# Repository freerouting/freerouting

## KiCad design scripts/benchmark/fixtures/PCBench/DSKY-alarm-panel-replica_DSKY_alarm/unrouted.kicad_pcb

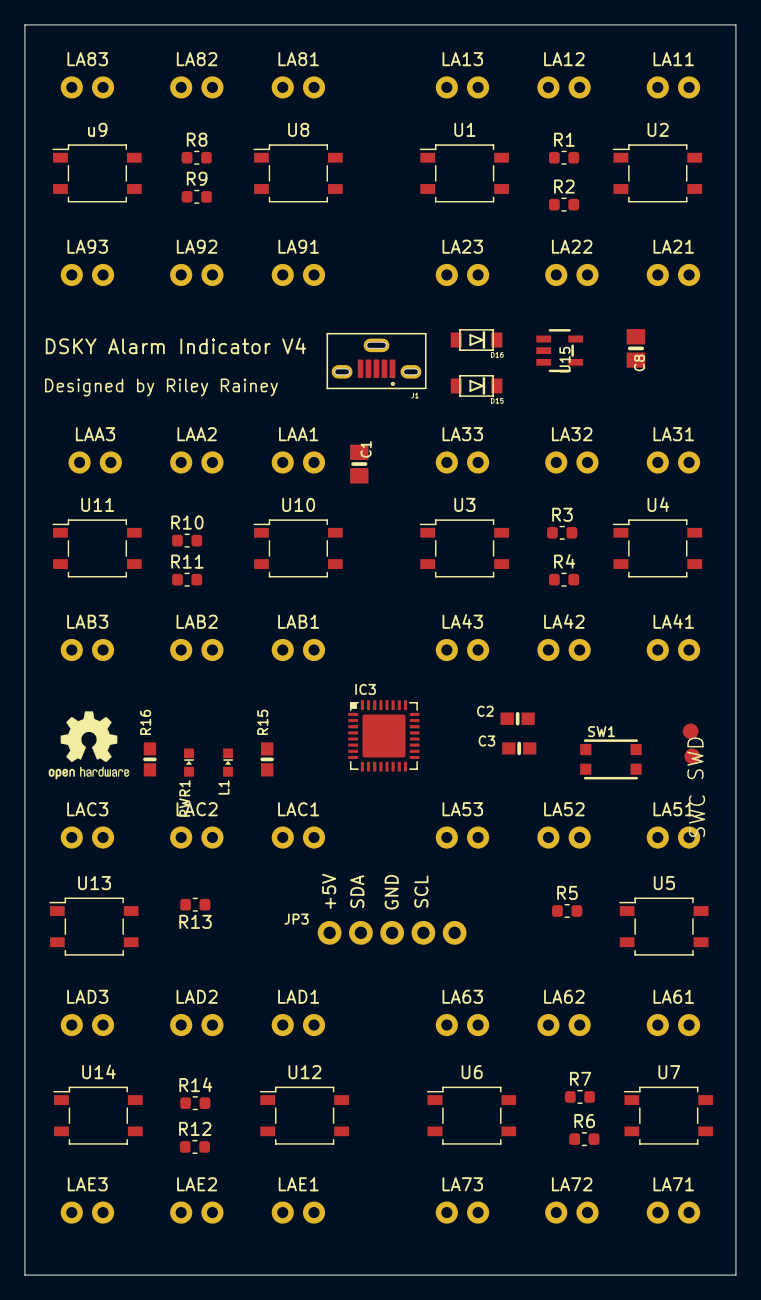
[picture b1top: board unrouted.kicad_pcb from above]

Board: 2 copper layers, 57.8 x 101.6 mm, 87 parts (0 on the bottom side), 58 nets, no tracks yet.

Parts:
C1, C8: 10uF; 0805-NO
C2, C3: 1uF; 0603-NO
D15, D16: SCHOTTKY; SOD-123FL
IC3: ATSAMD21E; QFN32_5MM
J1: 105133-0001-MOLEX-USB; MOLEX_105133-0001
JP3: HEADER-1X576MIL; 1X05_ROUND_76
L1: red; CHIPLED_0603_NOOUTLINE
LA11, LA12, LA13, LA21, LA22, LA23, LA31, LA32, LA33, LA41, LA42, LA43, LA51, LA52, LA53, LA61, LA62, LA63, LA71, LA72, LA73, LA81, LA82, LA83, LA91, LA92, LA93: Lamp; VCC7216-ND
LAA1, LAA2, LAA3: Lamp; VCC7216-ND
LAB1, LAB2, LAB3: Lamp; VCC7216-ND
LAC1, LAC2, LAC3: Lamp; VCC7216-ND
LAD1, LAD2, LAD3: Lamp; VCC7216-ND
LAE1, LAE2, LAE3: Lamp; VCC7216-ND
PWR1: green; CHIPLED_0603_NOOUTLINE
R1, R2, R3, R4, R5, R6, R7, R8, R9, R10, R11, R12, R13, R14: 1.1K; R_0603_1608Metric
R15: 1.5K; 0603-NO
R16: 10K; 0603-NO
SW1: reset; BTN_KMR2_4.6X2.8
SWC: TPB1,27; B1,27
SWD: TPB1,27; B1,27
U1, U2, U3, U4, U5, U6, U7, U8, U10, U11, U12, U13, U14: AQY232SZ; SO-4_4.4x4.3mm_P2.54mm
U15: AP2112K-3.3; SOT23-5
u9: AQY232SZ; SO-4_4.4x4.3mm_P2.54mm

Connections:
3.3V: C2.1, C8.1, IC3.9, IC3.30, R16.2, U15.5
+5V: D16.A, JP3.1, LA11.2, LA12.2, LA13.2, LA21.2, LA22.2, LA23.2, LA31.2, LA32.2, LA33.2, LA41.2, LA42.2, LA43.2, LA51.2, LA52.2, LA53.2, LA61.2, LA62.2, LA63.2, LA71.2, LA72.2, LA73.2, LA81.2, LA82.2, LA83.2, LA91.2, LA92.2, LA93.2, LAA1.2, LAA2.2, LAA3.2, LAB1.2, LAB2.2, LAB3.2, LAC1.2, LAC2.2, LAC3.2, LAD1.2, LAD2.2, LAD3.2, LAE1.2, LAE2.2, LAE3.2
/D0_A4_PA08_SDA: IC3.11, JP3.2
/D2_A1_PA09_SCL_MISO: IC3.12, JP3.4
/D+: IC3.24, J1.3
/D-: IC3.23, J1.2
/VOUT: C1.1, D15.C, D16.C, U15.1, U15.3
/~RESET: IC3.26, SW1.A, SW1.A'
GND: C1.2, C2.2, C3.2, C8.2, IC3.10, IC3.28, IC3.33, J1.5, J1.S3, JP3.3, L1.C, PWR1.C, SW1.B, SW1.B', U1.2, U1.3, U2.2, U2.3, U3.2, U3.3, U4.2, U4.3, U5.2, U5.3, U6.2, U6.3, U7.2, U7.3, U8.2, U8.3, U10.2, U10.3, U11.2, U11.3, U12.2, U12.3, U13.2, U13.3, U14.2, U14.3, U15.2, u9.2, u9.3
LA1_PA02: IC3.3, R1.1
LA2_PA03: IC3.4, R2.1
LA3_PA04: IC3.5, R3.1
LA4_P05: IC3.6, R4.1
LA5_PA19: IC3.20, R5.1
LA6_PA22: IC3.21, R6.1
LA7_PA23: IC3.22, R7.1
LA8_PA27: IC3.25, R8.1
LA9_PA11: IC3.14, R9.1
LA10_PA14: IC3.15, R10.1
LA11_PA15: IC3.16, R11.1
LA12_PA16: IC3.17, R12.1
LA13_PA17: IC3.18, R13.1
LA14_PA18: IC3.19, R14.1
unnamed: C3.1, IC3.29
unnamed: IC3.13, R15.2
unnamed: IC3.31, SWC.TP
unnamed: IC3.32, SWD.TP
unnamed: L1.A, R15.1
unnamed: LA11.1, LA12.1, LA13.1, U1.4
unnamed: LA21.1, LA22.1, LA23.1, U2.4
unnamed: LA31.1, LA32.1, LA33.1, U3.4
unnamed: LA41.1, LA42.1, LA43.1, U4.4
unnamed: LA51.1, LA52.1, LA53.1, U5.4
unnamed: LA61.1, LA62.1, LA63.1, U6.4
unnamed: LA71.1, LA72.1, LA73.1, U7.4
unnamed: LA81.1, LA82.1, LA83.1, U8.4
unnamed: LA91.1, LA92.1, LA93.1, u9.4
unnamed: LAA1.1, LAA2.1, LAA3.1, U10.4
unnamed: LAB1.1, LAB2.1, LAB3.1, U11.4
unnamed: LAC1.1, LAC2.1, LAC3.1, U12.4
unnamed: LAD1.1, LAD2.1, LAD3.1, U13.4
unnamed: LAE1.1, LAE2.1, LAE3.1, U14.4
unnamed: PWR1.A, R16.1
unnamed: R1.2, U1.1
unnamed: R2.2, U2.1
unnamed: R3.2, U3.1
unnamed: R4.2, U4.1
unnamed: R5.2, U5.1
unnamed: R6.2, U6.1
unnamed: R7.2, U7.1
unnamed: R8.2, U8.1
unnamed: R9.2, u9.1
unnamed: R10.2, U10.1
unnamed: R11.2, U11.1
unnamed: R12.2, U12.1
unnamed: R13.2, U13.1
unnamed: R14.2, U14.1
VBUS: D15.A, J1.1

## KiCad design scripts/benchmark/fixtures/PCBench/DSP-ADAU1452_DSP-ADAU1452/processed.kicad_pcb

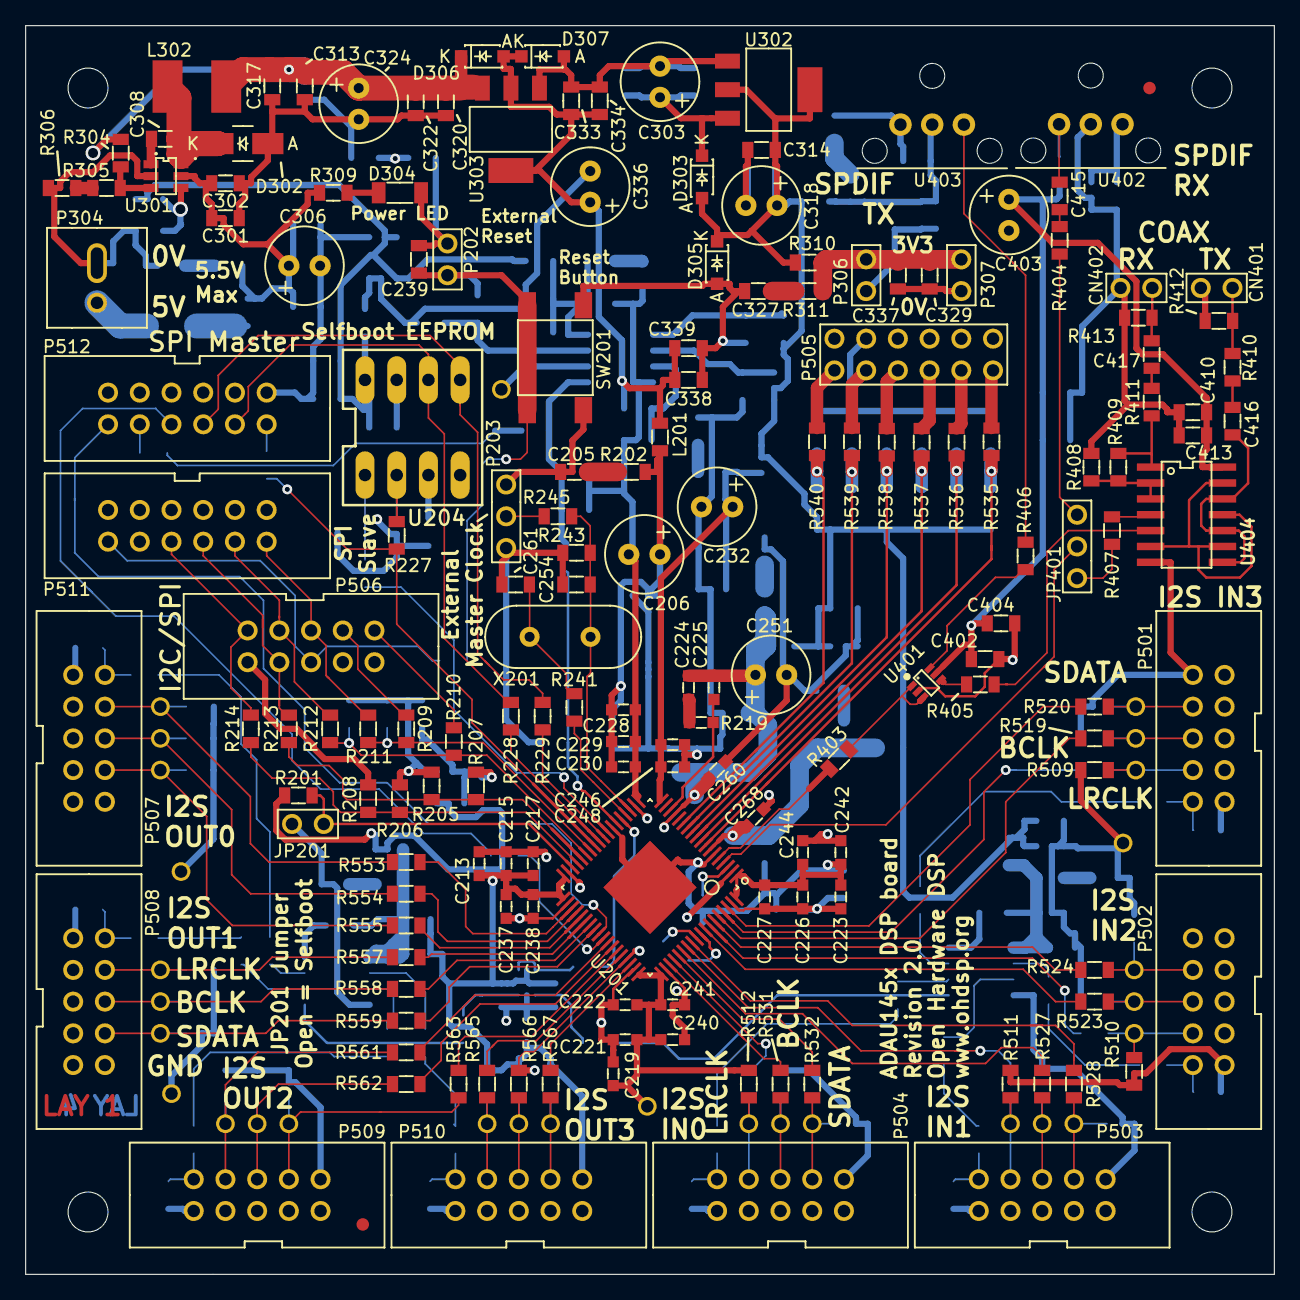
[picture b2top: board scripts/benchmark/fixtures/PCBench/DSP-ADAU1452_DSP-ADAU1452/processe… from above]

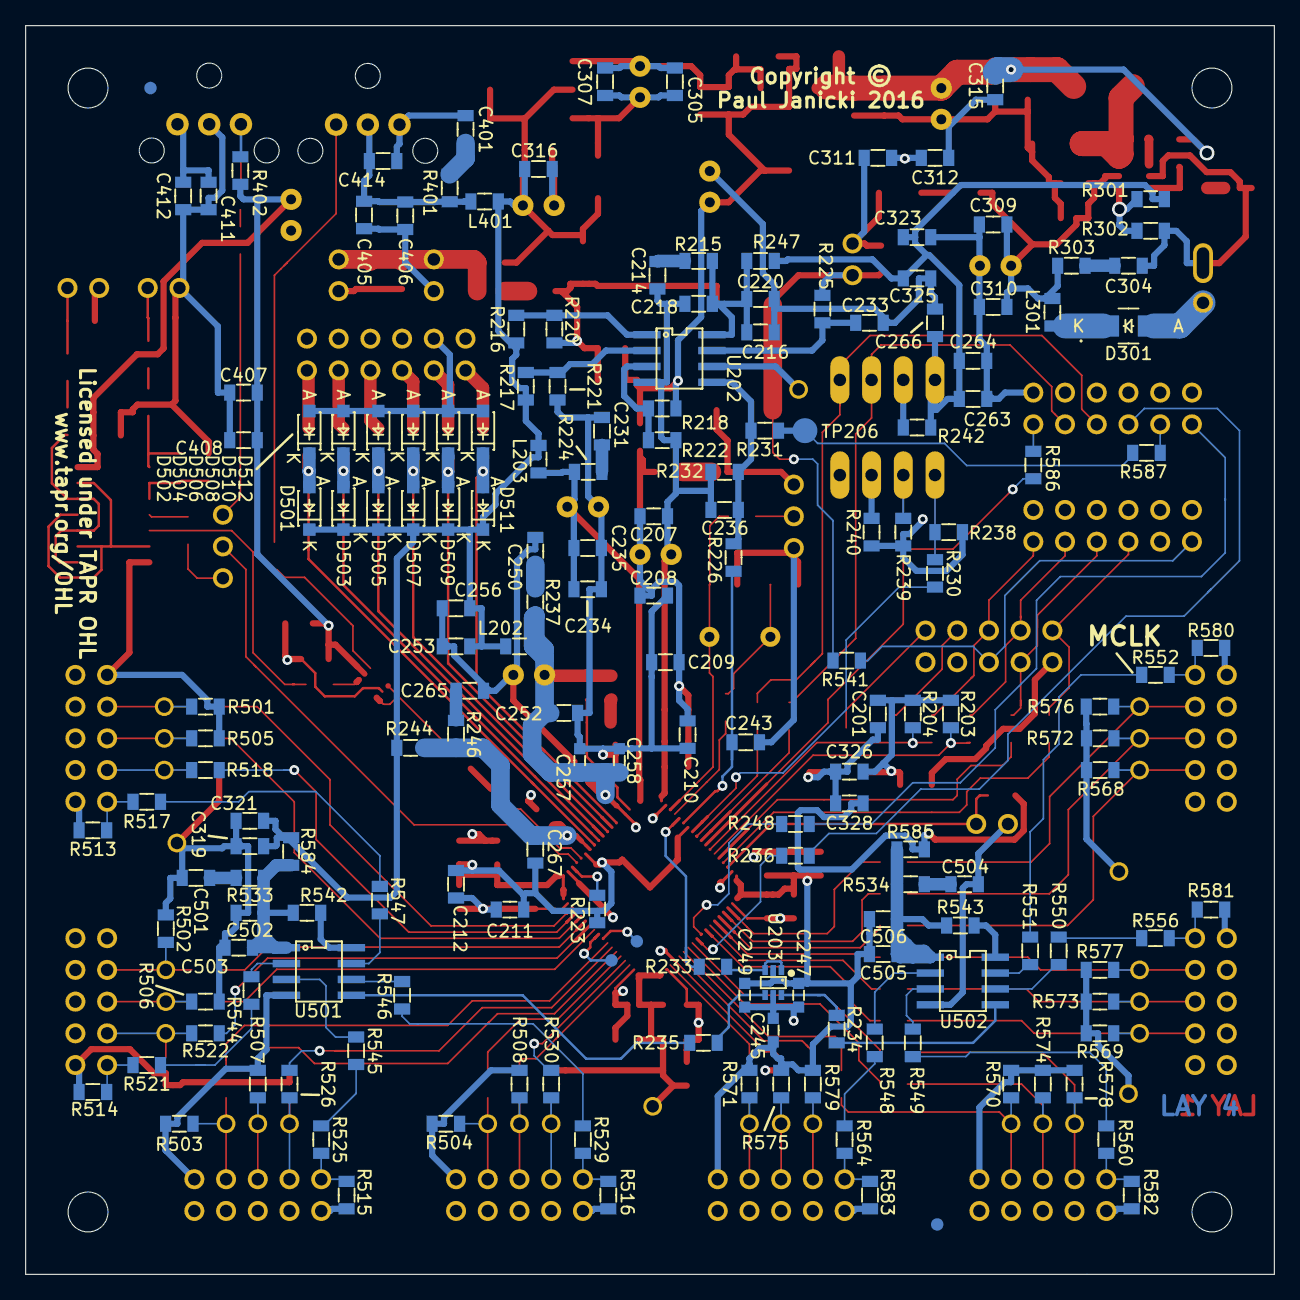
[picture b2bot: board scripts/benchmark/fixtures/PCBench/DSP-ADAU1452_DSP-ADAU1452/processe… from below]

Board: 4 copper layers, 100.0 x 100.0 mm, 377 parts (177 on the bottom side), 190 nets.

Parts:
C201, C208, C210, C212, C218, C233, C235, C236, C239, C243, C253, C264, C302, C307, C310, C314, C317, C319, C320, C323, C326, C329, C333, C338, C402, C406, C412, C413, C414, C416, C417, C503, C506: 100n; SMD-0805
C205, C214, C231, C250, C265, C304, C327, C401, C501, C504: 100p; SMD-0805
C206, C232, C251, C303, C306, C318, C324, C336, C403: 220u; CAP-TH-D6.3mmP2.5mm
C207, C234, C252, C267, C301, C305, C309, C313, C315, C316, C322, C334, C405, C502, C505: 22u; SMD-0805
C209, C211, C216, C256, C266, C321, C325, C328, C337, C339, C404, C410, C411: 10u; SMD-0805
C213, C219, C223, C228, C237, C240, C242, C245, C246, C257: 1u; SMD-0603
C215, C221, C226, C229, C238, C241, C244, C247, C248, C258, C268: 100n; SMD-0603
C217, C222, C227, C230, C249, C260: 10n; SMD-0603
C220, C263, C308, C415: 10n; SMD-0805
C224: 5n6; SMD-0603
C225: 150p; SMD-0603
C254, C261: 33p; SMD-0805
C311, C312, C407, C408: N/F; SMD-0805
CN401, CN402: COAX; CONN_SIL_2_1MM
D301, D302: B240A; DIODE-SMA
D303, D305, D306, D307, D501, D502, D503, D504, D505, D506, D507, D508, D509, D510, D511, D512: SS14L; DIODE-SOD-123
D304: Green LED 1206; SMD-1206
FID1, FID2, FID3, FID4: MNT_HOLE; FID-1MM-3MM
JP201: CONN_2x1; CONN_SIL_2_1MM
JP401: CONN_3x1; CONN_SIL_3_1MM
L201, L202, L203, L301, L401: 600R@100MHz; SMD-0805
L302: TYS50404R7N-10; IND-TYS5040-HS
MNT301, MNT302, MNT303, MNT304: MNT_HOLE; MNT_HOLE_3.2mm
P202, P306, P307: CONN_2x1; CONN_SIL_2_1MM
P203: CONN_3x1; CONN_SIL_3_1MM
P304: CONN_2x1; CONN-2WAY-2.54mm-3.81mm-SPACING
P501, P502, P503, P504, P506, P507, P508, P509, P510: CONN_02X05; CONN_DIL_2X5_BOX_1MM
P505: CONN_02X06; CONN_DIL_2X6_1MM
P511, P512: CONN_02X06; CONN_DIL_2X6_BOX_1MM
R201, R225, R542, R543: 1k; SMD-0805
R202, R215, R224, R237, R246, R303, R311, R401, R533, R534: 47; SMD-0805
R203, R204, R205, R206, R207, R208, R209, R210, R220, R239, R243, R245, R501, R502, R503, R504, R505, R506, R507, R508, R509, R510, R511, R512, R513, R514, R515, R516, R568, R569, R570, R571, R572, R573, R574, R575, R576, R577, R578, R579, R580, R581, R582, R583: N/F; SMD-0805
R211, R227, R228, R229, R230, R233, R234, R235, R236, R248, R403, R404, R405, R406, R407, R413, R544, R545, R546, R547, R548, R549, R550, R551, R553, R554, R555, R557, R558, R559, R561, R562, R563, R565, R566, R567: 75; SMD-0805
R212, R213, R214, R216, R223, R306, R517, R518, R519, R520, R521, R522, R523, R524, R525, R526, R527, R528, R529, R530, R531, R532, R541, R552, R556, R560, R564, R586, R587: 0; SMD-0805
R217: 12k; SMD-0805
R218: 3k3; SMD-0805
R219: 4k3; SMD-0603
R221: 3k; SMD-0805
R222: 3k6; SMD-0805
R226, R231, R241, R411: 100; SMD-0805
R232: 100k; SMD-0805
R238, R240, R242, R302, R402, R408, R409: 10k; SMD-0805
R244, R247, R310, R584, R585: 1; SMD-0805
R301: 16k; SMD-0805
R304: 24k; SMD-0805
R305: 15k; SMD-0805
R309: 470; SMD-0805
R410: 360; SMD-0805
R412: 91; SMD-0805
R535, R536, R537, R538, R539, R540: 4k7; SMD-0805
SW201: SWITCH; SW_TACT_SMD
TP201, TP501, TP502, TP503, TP504, TP505, TP506, TP507, TP508, TP509, TP510, TP511, TP512, TP513, TP514, TP515, TP516, TP517, TP518, TP519, TP520, TP521, TP522, TP523, TP524, TP525, TP526, TP527, TP528: PIN; TP-TH-1mm
TP204, TP205: PIN; TP-1mm
TP206: PIN; TP-2mm
U201: ADAU1452WBCPZ; IC-LFCSP72-HANDFIT
U202: ADM13307-5ARZ; IC_SOIC_8
U203: NC7WZ17P6X; IC-SC70-6
U204: 25AA1024; IC_DIP_8
U301: ADP2301AUJZ; IC-SOT23-6
U302: TLV1117LV33DCY; IC-SOT-223
U303: TLV1117LV12DCY; IC-SOT-223
U401: NC7WZ16P6X; IC-SC70-6
U402: IC-SPDIF-RX-OPTO; IC_SPDIF_OPTO
U403: IC-SPDIF-TX-OPTO; IC_SPDIF_OPTO
U404: 74HC04; IC_SOIC_14
U501, U502: NB3L553; IC_SOIC_8
X201: 24M576; XTAL_HC49_TH

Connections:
/ADAU1452/ADAU_SPDIF_RX: JP401.2, U201.4
/ADAU1452/ADAU_SPDIF_TX: R403.2, U201.5
/ADAU1452/ADCIN_BCLK0: R531.2, U201.57
/ADAU1452/ADCIN_BCLK1: R527.2, U201.60
/ADAU1452/ADCIN_BCLK2: R523.2, U201.65
/ADAU1452/ADCIN_BCLK3: R519.2, U201.68
/ADAU1452/ADCIN_LRCLK0: R530.2, U201.58
/ADAU1452/ADCIN_LRCLK1: R526.2, U201.61
/ADAU1452/ADCIN_LRCLK2: R522.2, U201.66
/ADAU1452/ADCIN_LRCLK3: R518.2, U201.69
/ADAU1452/ADCIN_SDATA0: R532.2, U201.59
/ADAU1452/ADCIN_SDATA1: R528.2, U201.62
/ADAU1452/ADCIN_SDATA2: R524.2, U201.67
/ADAU1452/ADCIN_SDATA3: R520.2, U201.70
/ADAU1452/AVDD: C267.1, C268.1, R244.1, R246.1, U201.7
/ADAU1452/DACOUT_BCLK0: R554.1, U201.40
/ADAU1452/DACOUT_BCLK1: R558.1, U201.43
/ADAU1452/DACOUT_BCLK2: R562.1, U201.48
/ADAU1452/DACOUT_BCLK3: R566.1, U201.51
/ADAU1452/DACOUT_LRCLK0: R553.1, U201.39
/ADAU1452/DACOUT_LRCLK1: R557.1, U201.42
/ADAU1452/DACOUT_LRCLK2: R561.1, U201.47
/ADAU1452/DACOUT_LRCLK3: R565.1, U201.50
/ADAU1452/DACOUT_SDATA0: R555.1, U201.41
/ADAU1452/DACOUT_SDATA1: R559.1, U201.44
/ADAU1452/DACOUT_SDATA2: R563.1, U201.49
/ADAU1452/DACOUT_SDATA3: R567.1, U201.52
/ADAU1452/DSP_RESET: C243.1, R226.1, U201.24
/ADAU1452/DVDD: C206.1, C207.1, C208.1, C209.1, C210.1, C211.1, C212.1, C213.1, C215.1, C217.1, C219.1, C221.1, C222.1, C223.1, C226.1, C227.1, C228.1, C229.1, C230.1, L201.2, R202.1, U201.20, U201.35, U201.53, U201.71
/ADAU1452/GLB_RESET: R231.1, R587.2, TP206.1
/ADAU1452/I2C_SCL: P506.1, R210.1
/ADAU1452/I2C_SDA: P506.3, R209.1
/ADAU1452/IOVDD: C232.1, C234.1, C235.1, C237.1, C238.1, C240.1, C241.1, C242.1, C244.1, C245.1, C246.1, C247.1, C248.1, C249.1, L203.2, R224.1, U201.2, U201.18, U201.38, U201.56, U203.5
/ADAU1452/MAN_RST_IN: C239.1, P202.1, R225.2, R541.2, SW201.1
/ADAU1452/MCLK: R235.1, U501.5
/ADAU1452/MCLK2: R234.1, U502.5
/ADAU1452/MCLK_ADAU: R233.2, U201.23
/ADAU1452/MISO/SDA: R204.2, R209.2, R211.2, U201.30
/ADAU1452/MOSI/ADDR1: R205.2, R207.2, R213.2, U201.32
/ADAU1452/M_SS: R230.2, R238.2, U204.1
/ADAU1452/PVDD: C224.1, C225.1, C251.1, C252.1, C257.1, C258.1, C260.1, L202.2, R237.1, U201.15
/ADAU1452/SCLK/SCL: R203.2, R210.2, R212.2, U201.31
/ADAU1452/SELFBOOT: JP201.1, R201.2, U201.34
/ADAU1452/SPI_MISO: P506.5, P511.2, R211.1
/ADAU1452/SPI_MOSI: P506.8, P511.6, R213.1
/ADAU1452/SPI_SCLK: P506.7, P511.4, R212.1
/ADAU1452/SPI_SS: P506.9, P511.8, R214.1
/ADAU1452/SS/ADDR0: R206.2, R208.2, R214.2, U201.33
/ADAU1452/XTALIN: C254.1, R243.1, R245.1, U201.21, X201.1
/ADAU1452/XTALOUT: R241.1, U201.22
/Connectors/AUXADCIN_1: D501.1, D502.2, R535.2, U201.8
/Connectors/AUXADCIN_2: D503.1, D504.2, R536.2, U201.9
/Connectors/AUXADCIN_3: D505.1, D506.2, R537.2, U201.10
/Connectors/AUXADCIN_4: D507.1, D508.2, R538.2, U201.11
/Connectors/AUXADCIN_5: D509.1, D510.2, R539.2, U201.12
/Connectors/AUXADCIN_6: D511.1, D512.2, R540.2, U201.13
/Connectors/I2C_RST: P506.6, P511.12, R541.1
/Connectors/MCLKA1: R529.2, R546.1
/Connectors/MCLKA2: R525.2, R545.1
/Connectors/MCLKA3: R521.2, R544.1
/Connectors/MCLKA4: R517.2, R547.1
/Connectors/MCLKB1: R551.1, R552.1
/Connectors/MCLKB2: R550.1, R556.1
/Connectors/MCLKB3: R549.1, R560.1
/Connectors/MCLKB4: R548.1, R564.1
/Connectors/M_MUTE: P512.12, R248.2
/Connectors/M_SPI_MISO: R227.1, R586.2, U201.29
/Connectors/M_SPI_MOSI: P512.6, R229.2, U204.5
/Connectors/M_SPI_SCLK: P512.4, R228.2, U204.6
/Connectors/M_SPI_SS: P512.8, R236.2
/Power Supply/2V1: C313.1, C315.1, C317.1, C320.1, C322.1, C324.1, D306.2, L302.2, R304.2, U303.3
GNDD: C201.2, C205.2, C206.2, C207.2, C208.2, C209.2, C210.2, C211.2, C212.2, C213.2, C214.2, C215.2, C216.2, C217.2, C218.2, C219.2, C220.2, C221.2, C222.2, C223.2, C226.2, C227.2, C228.2, C229.2, C230.2, C231.2, C232.2, C233.2, C234.2, C235.2, C236.2, C237.2, C238.2, C239.2, C240.2, C241.2, C242.2, C243.2, C244.2, C245.2, C246.2, C247.2, C248.2, C249.2, C250.2, C251.2, C252.2, C253.2, C254.2, C256.2, C257.2, C258.2, C260.2, C261.2, C263.2, C264.2, C265.2, C266.2, C267.2, C268.2, C301.1, C302.1, C303.2, C304.2, C305.2, C306.2, C307.2, C309.1, C310.1, C311.1, C312.1, C313.2, C314.2, C315.2, C316.2, C317.2, C318.2, C319.2, C320.2, C321.2, C322.2, C323.2, C324.2, C325.2, C326.2, C327.2, C328.2, C329.2, C333.2, C334.2, C336.2, C337.2, C338.2, C339.2, C401.2, C402.2, C403.2, C404.2, C405.2, C406.2, C407.2, C408.2, C410.2, C411.2, C412.2, C413.2, C414.2, C501.2, C502.2, C503.2, C504.2, C505.2, C506.2, CN401.2, CN402.2, D302.1, D304.2, D305.1, D307.1, D502.1, D504.1, D506.1, D508.1, D510.1, D512.1, JP201.2, P202.2, P203.1, P203.3, P304.2, P306.2, P307.2, P501.1, P501.3, P501.5, P501.7, P501.9, P501.10, P502.1, P502.3, P502.5, P502.7, P502.9, P502.10, P503.1, P503.3, P503.5, P503.7, P503.9, P503.10, P504.1, P504.3, P504.5, P504.7, P504.9, P504.10, P505.1, P505.3, P505.5, P505.7, P505.9, P505.11, P506.10, P507.1, P507.3, P507.5, P507.7, P507.9, P507.10, P508.1, P508.3, P508.5, P508.7, P508.9, P508.10, P509.1, P509.3, P509.5, P509.7, P509.9, P509.10, P510.1, P510.3, P510.5, P510.7, P510.9, P510.10, P511.1, P511.3, P511.5, P511.7, P511.9, P511.11, P512.1, P512.3, P512.5, P512.7, P512.9, P512.11, R207.1, R208.1, R220.1, R221.1, R222.1, R223.1, R232.1, R243.2, R302.1, R306.1, R408.1, R412.1, R413.1, R501.1, R502.1, R503.1, R504.1, R505.1, R506.1, R507.1, R508.1, R509.1, R510.1, R511.1, R512.1, R513.1, R514.1, R515.1, R516.1, R568.1, R569.1, R570.1, R571.1, R572.1, R573.1, R574.1, R575.1, R576.1, R577.1, R578.1, R579.1, R580.1, R581.1, R582.1, R583.1, SW201.2, TP513.1, TP514.1, TP515.1, TP516.1, U201.1, U201.6, U201.19, U201.25, U201.36, U201.37, U201.54, U201.55, U201.72, U201.EP1, U202.4, U203.2, U204.4, U301.2, U302.1, U303.1, U401.2, U402.2, U403.3, U404.7, U501.4, U502.4
unnamed: C205.1, R202.2
unnamed: C214.1, R215.2
unnamed: C216.1, C218.1, C220.1, R215.1, R247.1, U202.8
unnamed: C224.2, R219.1
unnamed: C225.2, R219.2, U201.16
unnamed: C231.1, R224.2
unnamed: C233.1, R225.1, U202.7
unnamed: C236.1, R226.2, R231.2, R232.2, U202.5
unnamed: C250.1, R237.2
unnamed: C261.1, R241.2, X201.2
unnamed: C265.1, R246.2
unnamed: C304.1, R303.2
unnamed: C308.1, U301.1
unnamed: C308.2, D302.2, L302.1, U301.6
unnamed: C327.1, R311.2
unnamed: C329.1, C337.1, P306.1, P307.1, R310.1, R311.1
unnamed: C401.1, R401.2
unnamed: C402.1, C403.1, C404.1, C405.1, C406.1, C407.1, C408.1, C410.1, C411.1, C412.1, C413.1, C414.1, L401.2, R401.1, R402.1, U401.5, U402.1, U403.2, U404.14
unnamed: C415.1, R404.2
unnamed: C415.2, R402.2, U402.3
unnamed: C416.1, R410.2
unnamed: C416.2, U404.8, U404.10, U404.12
unnamed: C417.1, R411.2
unnamed: C417.2, CN402.1, R413.2
unnamed: C501.1, R533.2
unnamed: C502.1, C503.1, R533.1, R542.2, R584.2, U501.1
unnamed: C504.1, R534.2
unnamed: C505.1, C506.1, R534.1, R543.2, R585.2, U502.1
unnamed: CN401.1, R410.1, R412.2
unnamed: D301.1, P304.1
unnamed: D301.2, L301.1
unnamed: D304.1, R309.2
unnamed: JP401.1, R404.1
unnamed: JP401.3, R407.2
unnamed: P203.2, R245.2
unnamed: P501.2, R513.2, R517.1
unnamed: P501.4, R509.2, R518.1, TP501.1
unnamed: P501.6, R505.2, R519.1, TP505.1
unnamed: P501.8, R501.2, R520.1, TP506.1
unnamed: P502.2, R514.2, R521.1
unnamed: P502.4, R510.2, R522.1, TP502.1
unnamed: P502.6, R506.2, R523.1, TP507.1
unnamed: P502.8, R502.2, R524.1, TP508.1
unnamed: P503.2, R515.2, R525.1
unnamed: P503.4, R511.2, R526.1, TP503.1
unnamed: P503.6, R507.2, R527.1, TP509.1
unnamed: P503.8, R503.2, R528.1, TP510.1
unnamed: P504.2, R516.2, R529.1
unnamed: P504.4, R512.2, R530.1, TP504.1
unnamed: P504.6, R508.2, R531.1, TP511.1
unnamed: P504.8, R504.2, R532.1, TP512.1
unnamed: P505.2, R535.1
unnamed: P505.4, R536.1
unnamed: P505.6, R537.1
unnamed: P505.8, R538.1
unnamed: P505.10, R539.1
unnamed: P505.12, R540.1
unnamed: P507.2, R552.2, R580.2
unnamed: P507.4, R553.2, R576.2, TP517.1
unnamed: P507.6, R554.2, R572.2, TP521.1
unnamed: P507.8, R555.2, R568.2, TP522.1
unnamed: P508.2, R556.2, R581.2
unnamed: P508.4, R557.2, R577.2, TP518.1
unnamed: P508.6, R558.2, R573.2, TP523.1
unnamed: P508.8, R559.2, R569.2, TP524.1
unnamed: P509.2, R560.2, R582.2
unnamed: P509.4, R561.2, R578.2, TP519.1
unnamed: P509.6, R562.2, R574.2, TP525.1
unnamed: P509.8, R563.2, R570.2, TP526.1
unnamed: P510.2, R564.2, R583.2
unnamed: P510.4, R565.2, R579.2, TP520.1
unnamed: P510.6, R566.2, R575.2, TP527.1
unnamed: P510.8, R567.2, R571.2, TP528.1
unnamed: P512.2, R586.1
unnamed: P512.10, R587.1
unnamed: R216.2, R220.2, U202.1
unnamed: R217.2, R221.2, U202.2
unnamed: R218.2, R222.2, U202.3
unnamed: R223.2, U201.3
unnamed: R227.2, R239.2, U204.2
unnamed: R228.1, U201.28
unnamed: R229.1, U201.27
unnamed: R230.1, U201.26
unnamed: R233.1, U203.1, U203.3
unnamed: R234.2, U203.6
unnamed: R235.2, U203.4
unnamed: R236.1, U201.46
unnamed: R240.2, U204.3
unnamed: R242.2, U204.7
unnamed: R248.1, U201.45
unnamed: R301.1, R302.2, U301.4
unnamed: R304.1, R305.2, U301.3
unnamed: R305.1, R306.2
unnamed: R403.1, U401.1, U401.3
unnamed: R405.1, U404.5
unnamed: R405.2, U401.4
unnamed: R406.1, U401.6
unnamed: R406.2, U403.1
unnamed: R407.1, U404.4
unnamed: R408.2, R409.1, U404.2, U404.3
unnamed: R409.2, R411.1, U404.1
unnamed: R542.1, U501.8
unnamed: R543.1, U502.8
unnamed: R544.2, U501.2
unnamed: R545.2, U501.3
unnamed: R546.2, U501.6
unnamed: R547.2, U501.7
unnamed: R548.2, U502.2
unnamed: R549.2, U502.3
unnamed: R550.2, U502.6
unnamed: R551.2, U502.7
unnamed: TP201.1, U202.6
unnamed: TP204.1, U201.64
unnamed: TP205.1, U201.63
unnamed: U404.6, U404.9, U404.11, U404.13
VAA: C201.1, C253.1, C256.1, C263.1, C264.1, C266.1, C314.1, C316.1, C318.1, C319.1, C321.1, C323.1, C325.1, C326.1, C328.1, D303.1, D305.2, D501.2, D503.2, D505.2, D507.2, D509.2, D511.2, L202.1, L203.1, L401.1, R201.1, R203.1, R204.1, R205.1, R206.1, R216.1, R217.1, R238.1, R239.1, R240.1, R242.1, R244.2, R247.2, R301.2, R310.2, R584.1, R585.1, U204.8, U302.2
VCC: C301.2, C302.2, C303.1, C305.1, C306.1, C307.1, C309.2, C310.2, C311.2, C312.2, D303.2, L301.2, R303.1, R309.1, U301.5, U302.3
VDD: C333.1, C334.1, C336.1, C338.1, C339.1, D306.1, D307.2, L201.1, R218.1, U303.2

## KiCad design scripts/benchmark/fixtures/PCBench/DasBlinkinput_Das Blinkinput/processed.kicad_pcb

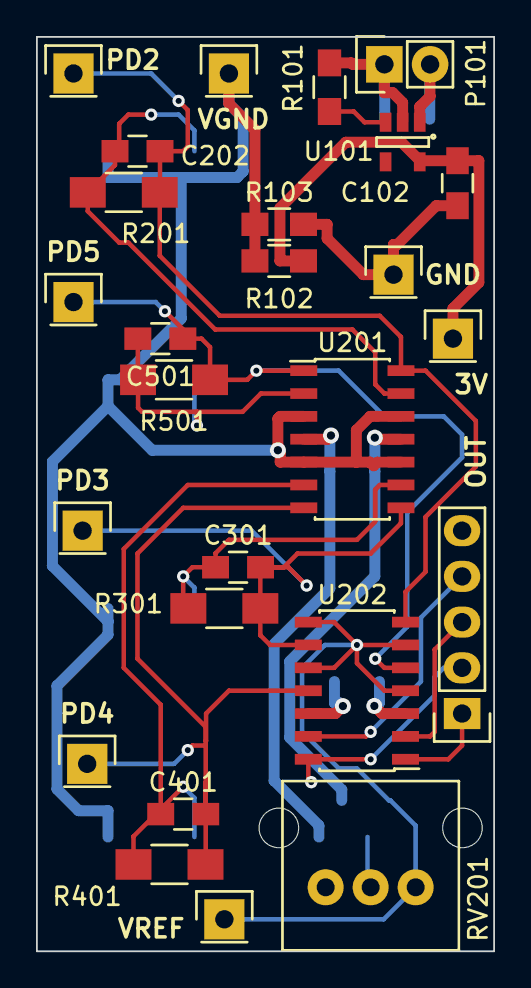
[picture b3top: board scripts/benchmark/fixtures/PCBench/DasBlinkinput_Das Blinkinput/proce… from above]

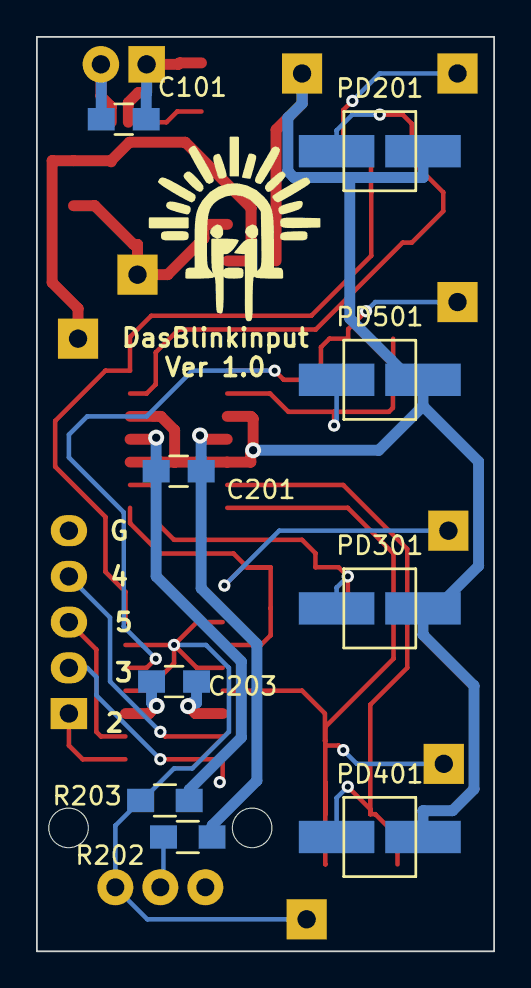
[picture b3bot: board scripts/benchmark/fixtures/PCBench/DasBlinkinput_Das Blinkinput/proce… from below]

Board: 4 copper layers, 25.4 x 50.8 mm, 35 parts (9 on the bottom side), 19 nets.

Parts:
C101, C102: 1U; C_0805_HandSoldering
C201, C203: .1U; C_0805_HandSoldering
C202, C301, C401, C501: 100p; C_0805_HandSoldering
P101: CONN_01X02; Pin_Header_Straight_1x02
P102, P103, P104, P106, P201, P301, P401, P501: CONN_01X01; Pin_Header_Straight_1x01
P105: CONN_01X05; Pin_Header_Straight_1x05
PD201, PD301, PD401, PD501: VBPW34SR; VPW34SR*
R101: 0; R_0805_HandSoldering
R102, R103, R202, R203: 10K; R_0805_HandSoldering
R201, R301, R401, R501: 1MEG; R_1206_HandSoldering
RV201: POT; P090L-02F25BR10K
U101: LP2980IM5-3.0/NOPB; SOT-23-5
U201: MCP6404; SOIC-14_3.9x8.7mm_Pitch1.27mm
U202: LM339; SOIC-14_3.9x8.7mm_Pitch1.27mm

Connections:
3V: C102.1, C201.2, C203.2, P103.1, R102.1, R203.2, U101.5, U201.4, U202.3
/Channel1Photodetect/PD2: P105.1, U202.1
/Channel2Photodetect/PD3: P105.2, U202.14
/Channel2Photodetect/REF_IN: P106.1, R202.2, RV201.3, U202.4, U202.6, U202.8, U202.10
/Channel3Photodetect/PD5: P105.3, U202.2
/Channel4Photodetect/PD4: P105.4, U202.13
GND: C101.2, C102.2, C201.1, C203.1, P101.1, P104.1, P105.5, R101.2, R103.2, R202.1, U101.2, U201.11, U202.12
unnamed: C101.1, P101.2, U101.1
unnamed: C202.1, P201.1, R201.1, U201.14, U202.7
unnamed: C202.2, PD201.2, R201.2, U201.13
unnamed: C301.1, P301.1, R301.1, U201.8, U202.9
unnamed: C301.2, PD301.2, R301.2, U201.9
unnamed: C401.1, P401.1, R401.1, U201.7, U202.11
unnamed: C401.2, PD401.2, R401.2, U201.6
unnamed: C501.1, P501.1, R501.1, U201.1, U202.5
unnamed: C501.2, PD501.2, R501.2, U201.2
unnamed: R101.1, U101.3
unnamed: R203.1, RV201.2
VGND: P102.1, PD201.1, PD301.1, PD401.1, PD501.1, R102.2, R103.1, U201.3, U201.5, U201.10, U201.12

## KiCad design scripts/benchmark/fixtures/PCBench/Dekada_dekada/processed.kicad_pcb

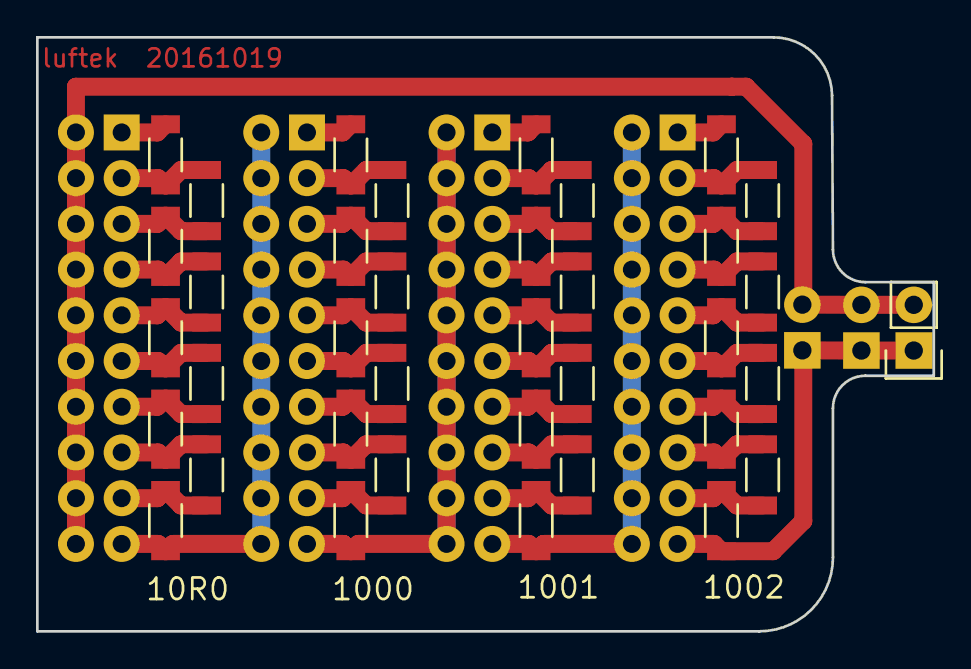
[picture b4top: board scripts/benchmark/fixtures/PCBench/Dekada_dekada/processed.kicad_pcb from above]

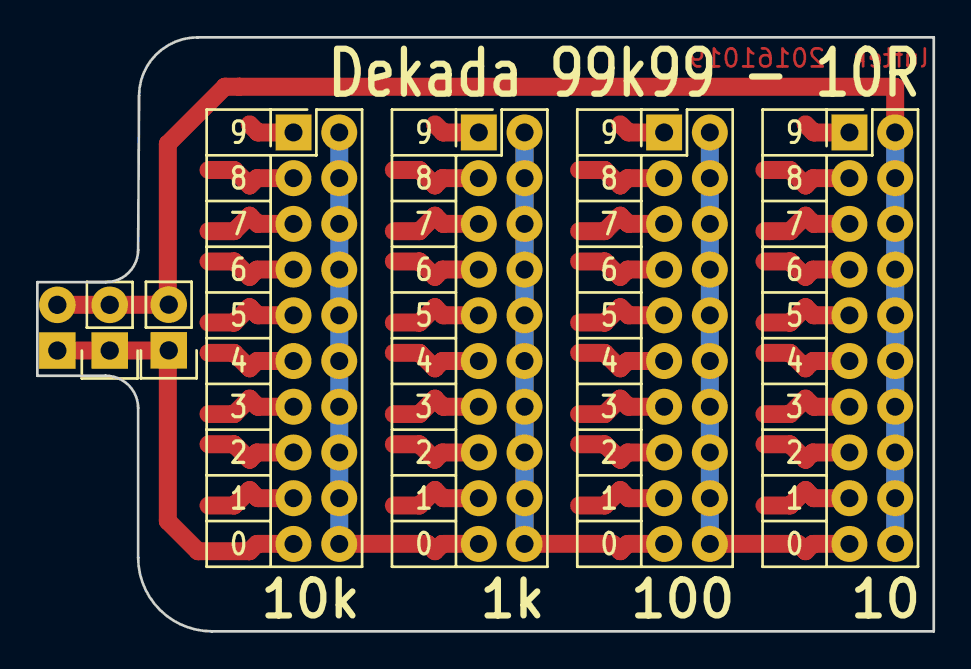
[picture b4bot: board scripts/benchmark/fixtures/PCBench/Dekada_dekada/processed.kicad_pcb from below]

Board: 2 copper layers, 49.8 x 33.0 mm, 43 parts (6 on the bottom side), 41 nets.

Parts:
P1, P2, P3, P4: CONN_02X10; Pin_Header_Straight_2x10_Custom
P5, P6, P7: CONN_01X02; Pin_Header_Straight_1x02
R1, R2, R3, R4, R5, R6, R7, R8, R9, R11, R12, R13, R14, R15, R16, R17, R18, R19, R21, R22, R23, R24, R25, R26, R27, R28, R29, R31, R32, R33, R34, R35, R36, R37, R38, R39: R; R_1206_Custom

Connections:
unnamed: P1.1, R1.2
unnamed: P1.3, R1.1, R2.2
unnamed: P1.5, R2.1, R3.2
unnamed: P1.7, R3.1, R4.2
unnamed: P1.9, R4.1, R5.2
unnamed: P1.2, P1.4, P1.6, P1.8, P1.10, P1.12, P1.14, P1.16, P1.18, P1.20, P5.2, P6.2, P7.2
unnamed: P1.11, R5.1, R6.2
unnamed: P1.13, R6.1, R7.2
unnamed: P1.15, R7.1, R8.2
unnamed: P1.17, R8.1, R9.2
unnamed: P1.19, P2.2, P2.4, P2.6, P2.8, P2.10, P2.12, P2.14, P2.16, P2.18, P2.20, R9.1
unnamed: P2.1, R11.2
unnamed: P2.3, R11.1, R12.2
unnamed: P2.5, R12.1, R13.2
unnamed: P2.7, R13.1, R14.2
unnamed: P2.9, R14.1, R15.2
unnamed: P2.11, R15.1, R16.2
unnamed: P2.13, R16.1, R17.2
unnamed: P2.15, R17.1, R18.2
unnamed: P2.17, R18.1, R19.2
unnamed: P2.19, P3.2, P3.4, P3.6, P3.8, P3.10, P3.12, P3.14, P3.16, P3.18, P3.20, R19.1
unnamed: P3.1, R21.2
unnamed: P3.3, R21.1, R22.2
unnamed: P3.5, R22.1, R23.2
unnamed: P3.7, R23.1, R24.2
unnamed: P3.9, R24.1, R25.2
unnamed: P3.11, R25.1, R26.2
unnamed: P3.13, R26.1, R27.2
unnamed: P3.15, R27.1, R28.2
unnamed: P3.17, R28.1, R29.2
unnamed: P3.19, P4.2, P4.4, P4.6, P4.8, P4.10, P4.12, P4.14, P4.16, P4.18, P4.20, R29.1
unnamed: P4.1, R31.2
unnamed: P4.3, R31.1, R32.2
unnamed: P4.5, R32.1, R33.2
unnamed: P4.7, R33.1, R34.2
unnamed: P4.9, R34.1, R35.2
unnamed: P4.11, R35.1, R36.2
unnamed: P4.13, R36.1, R37.2
unnamed: P4.15, R37.1, R38.2
unnamed: P4.17, R38.1, R39.2
unnamed: P4.19, P5.1, P6.1, P7.1, R39.1

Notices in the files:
scripts/benchmark/fixtures/PCBench/DSP-ADAU1452_DSP-ADAU1452/processed.kicad_pcb:
Licensed under the TAPR Open Hardware License (www.tapr.org/OHL). This documentation
Copyright Paul Janicki 2016
Copyright ©
Licensed under TAPR OHL
